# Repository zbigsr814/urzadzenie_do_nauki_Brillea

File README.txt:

# urzadzenie_do_nauki_Brillea

Wykonany projekt został zrealizowany dla koła naukowego Integral Senso na PŚ. 
 
Jest to urządzenie do nauki języka Brillea dla dzieci niedowidzących. Urządzenie odbierało dane z czujnika HC-05 (wyrazy/zdania) przesłane z telefonu (przez sieć Bluetooth) i wyświetlał je w alfabecie Brillea. Należało pobrać aplikację na telefon która funkcjonyje jako terminal Bluetooth. Wyświetlanie liter alfabetu Brillea odbywało się przez sześć diod, iteracja po kolejnych literach przez wciśnięcie przycisku. Regulacja jasności świecenia diodami potencjometrem. Sygnał z potencjometru trafiał na wejście analogowe Arduino. Regulacja świecenia diod przez PWM pinów wyjściowych Arduino. Zasilanie wewnętrzne bateryjne oraz zewnętrzne przewodem USB do źródła zasilania. Projekt obejmował: 

- Wykonanie programu na Arduino. Program odpowiedzialny za: obsługę odbioru danych przez Bluetooth, wysterowanie odpowiednich diod, sterowanie jasnością świecenia, odbiór danych z potencjometru.

- Projekt płytki PCB w Kicadzie. Płytka odpowiada m.in. za wzmocnienie sygnałów GPIO Arduino przez zastosowanie tranzystorów BC-547. Wzmocnione sygnały docierają na diody. Płytka pośredniczy między Arduino a resztą urządzenia. 
 
- Projekt obudowy urządzenia wykonanej w DesignSparks. Urządzenie miało być przeznaczone dla dzieci więc obudowa nie zawierała ostrych krawędzi, ścianki obudowy są odpowiednio grube. Wyznaczono sekcję dla zasilania bateryjnego i dla reszty elektroniki. Obudowę wykonano na drukarce 3D.

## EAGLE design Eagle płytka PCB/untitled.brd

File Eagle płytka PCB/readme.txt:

Pliki brd i sch w tym katalogu to gotowe pliki do uruchmienia w programie Kicad.

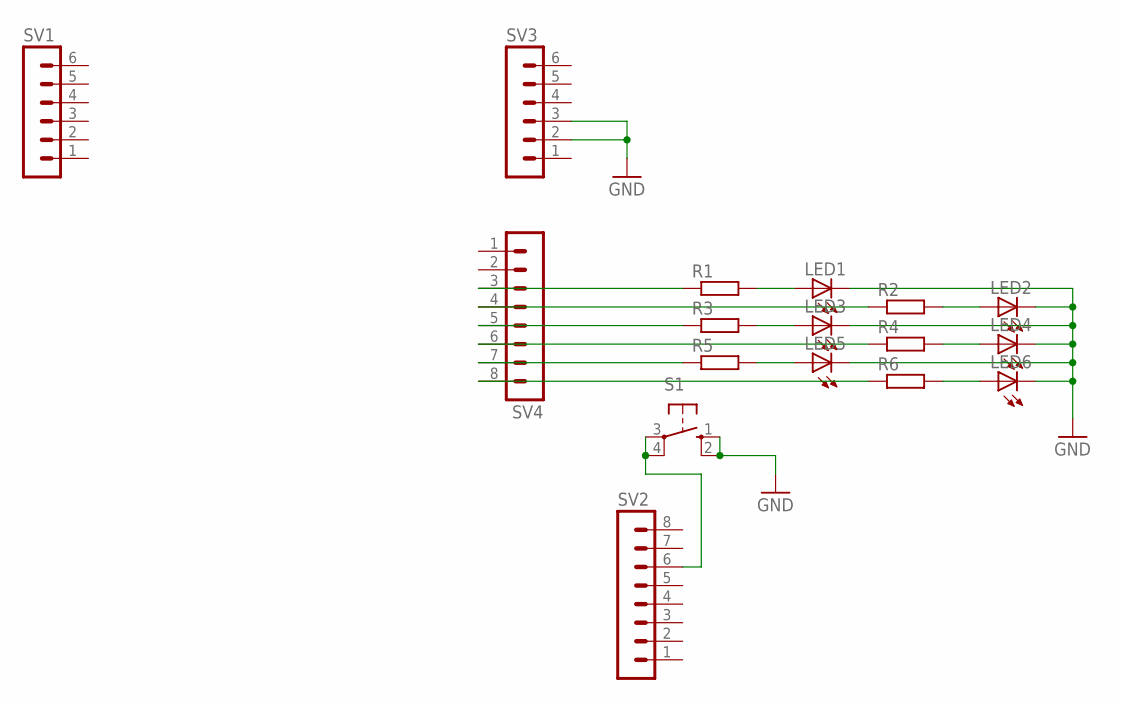
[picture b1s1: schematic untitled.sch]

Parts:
LED1, LED2, LED3, LED4, LED5, LED6: LED3MM
R1, R2, R3, R4, R5, R6: R-EU_0207/10; 0207/10
S1: 40-XX; B3F-40XX
SV1, SV3: MA06-1
SV2, SV4: MA08-1

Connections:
GND: LED1.K (C), LED2.K (C), LED3.K (C), LED4.K (C), LED5.K (C), LED6.K (C), S1.1 (S), S1.2 (S1), SV3.2, SV3.3
unnamed: R6.1, SV4.8
unnamed: LED4.A, R4.2
unnamed: R5.1, SV4.7
unnamed: LED2.A, R2.2
unnamed: LED3.A, R3.2
unnamed: R4.1, SV4.6
unnamed: R3.1, SV4.5
unnamed: LED1.A, R1.2
unnamed: LED5.A, R5.2
unnamed: R2.1, SV4.4
unnamed: R1.1, SV4.3
unnamed: LED6.A, R6.2
unnamed: S1.3, S1.4 (P1), SV2.6

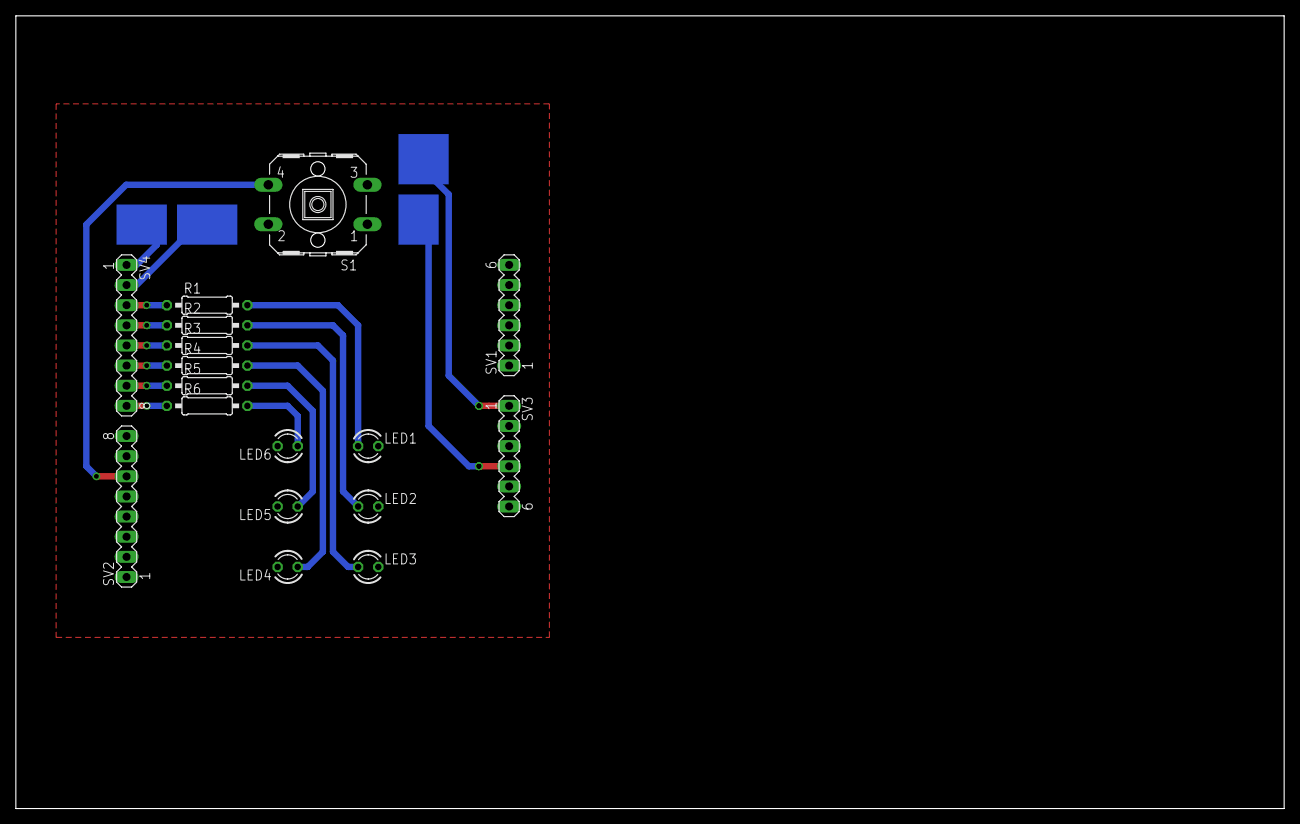
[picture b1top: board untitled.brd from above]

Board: 2 copper layers, 160.0 x 100.0 mm, 17 parts (0 on the bottom side), 14 nets.

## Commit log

2023-05-05 Projekt brillea
2023-05-11 zdj i film dodane
2025-06-15 Update readme.txt
    edited readme
